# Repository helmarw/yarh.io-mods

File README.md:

# yarh.io-mods
MODs for
[Y]ET [A]NOTHER [R]ASPBERRY [H]ANDHELD

original idea and files can be found here

https://yarh.io/yarh-io-mki.html

i added 5 programable GPIO buttons to the front and a custom made pcb (see kicad files) 
to connect the buttons and the RTC (or any other i2c device for that matter).
It can be hooked up to the free pinheader at the back of the LCD...

i uploded modified stl files for the frontpanel.
i also closed a few holes i didnt utilize and simplified the cabeling for my purpose.
Made a battery cover with place to store the stylus and
added a holder for a PureThermal2-UVC FLIR-camera to the housing.

The additional parts i used:

Prototype PCBs:

AZDelivery Set 16 x PCB Board
AZ-Delivery Vertriebs GmbH
https://www.amazon.de/dp/B078HV79XX/ref=cm_sw_em_r_mt_dp_2RHM7PPPENVQ2NX6XCZS?_encoding=UTF8&psc=1
or
ELEGOO Prototyp-Kit for DIY
ELEGOO Official US
https://www.amazon.com/dp/B072Z7Y19F/ref=cm_sw_em_r_mt_dp_VJY9EARDYE1PZMNZ06P7?_encoding=UTF8&psc=1

------------------------------------------------------------
Buttons:

YIXISI 180 pcs Button Micro Tactile Switch (4 pin 6x6mm 7x7mm)
YXS-DE
https://www.amazon.de/dp/B082ZL867J/ref=cm_sw_em_r_mt_dp_96NSV17K3W1S4MMYA5SG?_encoding=UTF8&psc=1
or
4 Pin Momentary Push Button Switch Sortiment Kit
BOJACK ELECTRON
Erfahren Sie mehr: https://www.amazon.com/dp/B07ZBHXBZ4/ref=cm_sw_em_r_mt_dp_M1YMZXK227A3NDJCXFJZ

------------------------------------------------------------

further information:

how to programm a shutdown button:
https://www.stderr.nl/Blog/Hardware/RaspberryPi/PowerButton.html

setting up gpio buttons via device tree overly (dtoverlay):
https://blog.gegg.us/2017/01/setting-up-a-gpio-button-keyboard-on-a-raspberry-pi/

howto use hwclock and delete fake-hwclock:
https://pimylifeup.com/raspberry-pi-rtc/

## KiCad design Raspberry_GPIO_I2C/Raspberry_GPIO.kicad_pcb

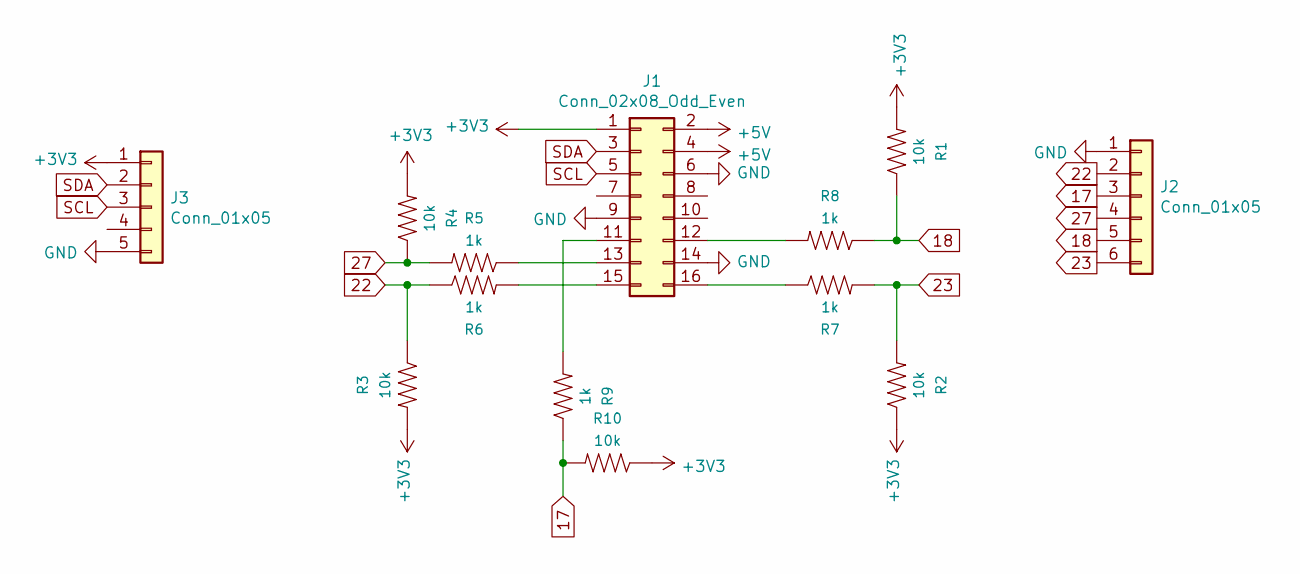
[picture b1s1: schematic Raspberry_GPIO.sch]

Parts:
J1: Conn_02x08_Odd_Even; PinSocket_2x08_P2.54mm_Vertical
J2: Conn_01x05; PinHeader_1x06_P2.54mm_Horizontal
J3: Conn_01x05; PinHeader_1x05_P2.54mm_Horizontal
R1, R2, R3, R4, R10: 10k; 1206
R5, R6, R7, R8, R9: 1k; 1206

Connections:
17: J2.3, R9.1, R10.2
18: J2.5, R1.1, R8.1
22: J2.2, R3.1, R6.1
23: J2.6, R2.2, R7.2
27: J2.4, R4.1, R5.2
+3V3: J1.1, J3.1, R1.2, R2.1, R3.2, R4.2, R10.1
+5V: J1.2, J1.4
GND: J1.6, J1.9, J1.14, J2.1, J3.5
unnamed: J1.11, R9.2
unnamed: J1.12, R8.2
unnamed: J1.13, R5.1
unnamed: J1.15, R6.2
unnamed: J1.16, R7.1
SCL: J1.5, J3.3
SDA: J1.3, J3.2

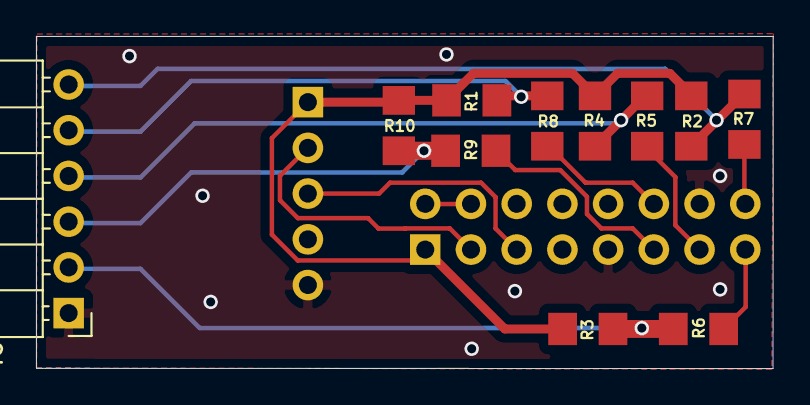
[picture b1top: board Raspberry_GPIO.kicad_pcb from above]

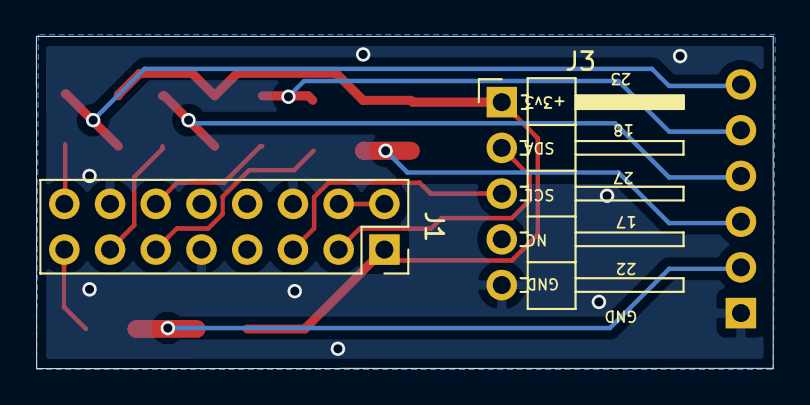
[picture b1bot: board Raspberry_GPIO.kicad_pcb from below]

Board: 2 copper layers, 40.9 x 18.5 mm, 13 parts (2 on the bottom side), 15 nets.

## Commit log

2021-04-06 correction
